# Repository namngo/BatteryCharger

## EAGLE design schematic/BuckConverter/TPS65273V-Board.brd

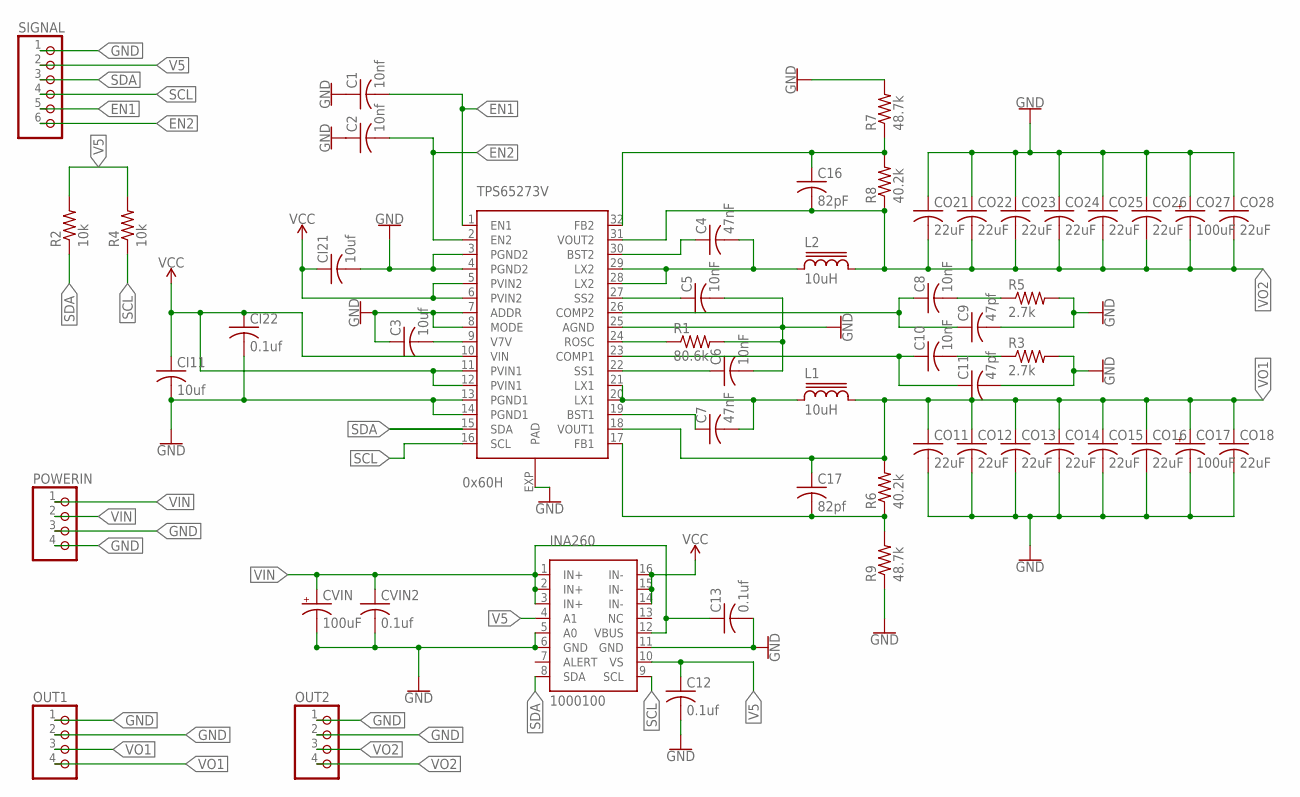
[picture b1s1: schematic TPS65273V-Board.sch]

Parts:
C1, C2: 10nf; C0805
C3: 10uf; C0805
C4, C7: 47nF; C0805
C5, C6, C8, C10: 10nF; C0805
C9, C11: 47pf; C0805
C12, C13: 0.1uf; C0805
C16: 82pF; C0805
C17: 82pf; C0805
CI11, CI21: 10uf; C1210
CI22: 0.1uf; C0805
CO11, CO12, CO13, CO14, CO15, CO16, CO18, CO21, CO22, CO23, CO24, CO25, CO26, CO28: 22uF; C0805
CO17, CO27: 100uF; PANASONIC_D
CVIN: 100uF; PANASONIC_D
CVIN2: 0.1uf; C0805
INA260: 1000100; TSSOP16
L1, L2: 10uH; MSS1048
OUT1, OUT2: PINHD-1X4; 1X04
POWERIN: PINHD-1X4; 1X04
R1: 80.6k; R0805
R2, R4: 10k; R0805
R3, R5: 2.7k; R0805
R6, R8: 40.2k; R0805
R7, R9: 48.7k; R0805
SIGNAL: PINHD-1X6; 1X06
TPS65273V: 0x60H; HTSSOP32DAP

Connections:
EN1: C1.2, SIGNAL.5, TPS65273V.1 (EN1)
EN2: C2.2, SIGNAL.6, TPS65273V.2 (EN2)
FB1: C17.2, R6.1, R9.2, TPS65273V.17 (FB1)
FB2: C16.1, R7.1, R8.2, TPS65273V.32 (FB2)
GND: C1.1, C2.1, C3.1, C5.2, C6.2, C9.2, C11.2, C12.2, C13.2, CI11.2, CI21.2, CI22.2, CO11.2, CO12.2, CO13.2, CO14.2, CO15.2, CO16.2, CO17.-, CO18.2, CO21.1, CO22.1, CO23.1, CO24.1, CO25.1, CO26.1, CO27.+, CO28.1, CVIN.-, CVIN2.2, INA260.5 (A0), INA260.6 (GND), INA260.11 (GND), OUT1.1, OUT1.2, OUT2.1, OUT2.2, POWERIN.3, POWERIN.4, R1.2, R3.2, R5.2, R7.2, R9.1, SIGNAL.1, TPS65273V.3 (PGND2), TPS65273V.4 (PGND2), TPS65273V.7 (ADDR), TPS65273V.8 (MODE), TPS65273V.13 (PGND1), TPS65273V.14 (PGND1), TPS65273V.25 (AGND), TPS65273V.EXP (PAD)
unnamed: C3.2, TPS65273V.9 (V7V)
unnamed: C4.2, L2.1, TPS65273V.28 (LX2), TPS65273V.29 (LX2)
unnamed: C4.1, TPS65273V.30 (BST2)
unnamed: C10.1, C11.1, TPS65273V.23 (COMP1)
unnamed: R1.1, TPS65273V.24 (ROSC)
unnamed: C10.2, R3.1
unnamed: C5.1, TPS65273V.27 (SS2)
unnamed: C8.1, C9.1, TPS65273V.26 (COMP2)
unnamed: C8.2, R5.1
unnamed: C6.1, TPS65273V.22 (SS1)
unnamed: C7.2, L1.1, TPS65273V.20 (LX1), TPS65273V.21 (LX1)
unnamed: C7.1, TPS65273V.19 (BST1)
SCL: INA260.9 (SCL), R4.1, SIGNAL.4, TPS65273V.16 (SCL)
SDA: INA260.8 (SDA), R2.1, SIGNAL.3, TPS65273V.15 (SDA)
V5: C12.1, INA260.4 (A1), INA260.10 (VS), R2.2, R4.2, SIGNAL.2
VCC: CI11.1, CI21.1, CI22.1, INA260.14 (IN-), INA260.15 (IN-), INA260.16 (IN-), TPS65273V.5 (PVIN2), TPS65273V.6 (PVIN2), TPS65273V.10 (VIN), TPS65273V.11 (PVIN1), TPS65273V.12 (PVIN1)
VIN: C13.1, CVIN.+, CVIN2.1, INA260.1 (IN+), INA260.2 (IN+), INA260.3 (IN+), INA260.12 (VBUS), POWERIN.1, POWERIN.2
VO1: C17.1, CO11.1, CO12.1, CO13.1, CO14.1, CO15.1, CO16.1, CO17.+, CO18.1, L1.2, OUT1.3, OUT1.4, R6.2, TPS65273V.18 (VOUT1)
VO2: C16.2, CO21.2, CO22.2, CO23.2, CO24.2, CO25.2, CO26.2, CO27.-, CO28.2, L2.2, OUT2.3, OUT2.4, R8.1, TPS65273V.31 (VOUT2)

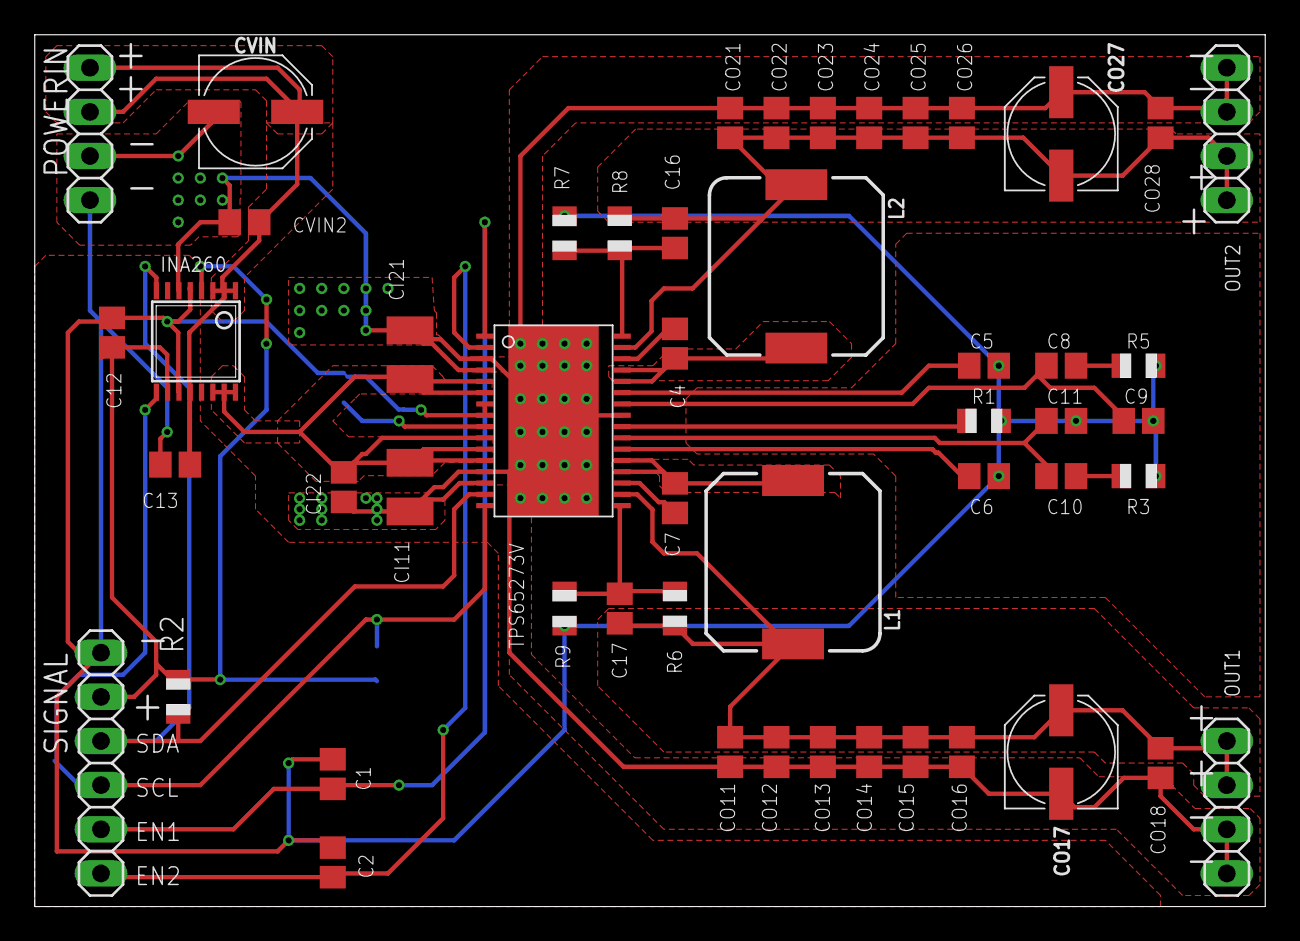
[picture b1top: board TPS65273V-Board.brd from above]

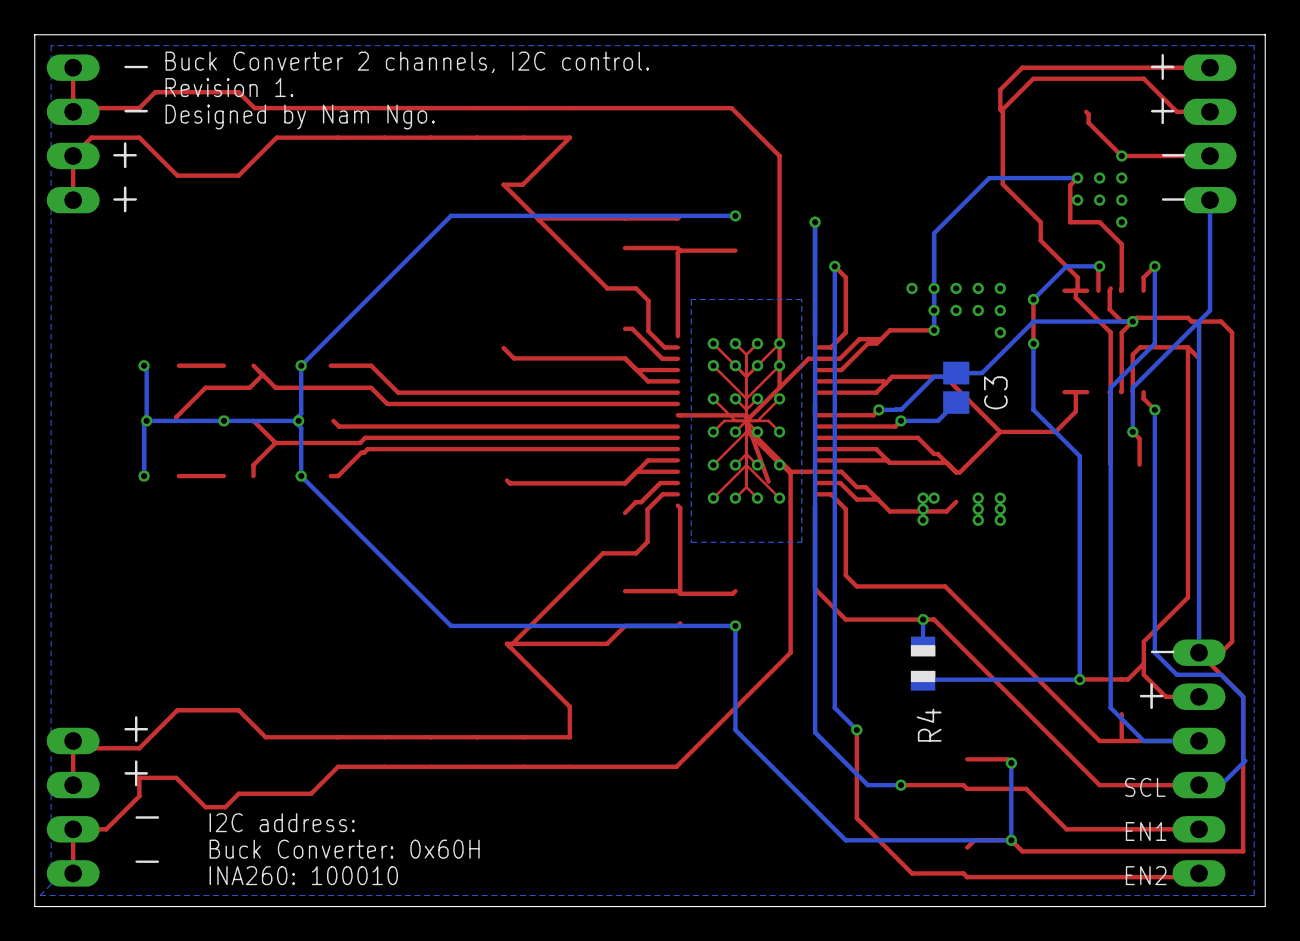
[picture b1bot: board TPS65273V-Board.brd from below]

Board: 2 copper layers, 70.8 x 50.2 mm, 53 parts (2 on the bottom side), 24 nets.

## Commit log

2017-09-09 first
2017-09-12 boards
2017-09-12 remove temp files
2017-09-13 files
2017-09-13 add gitignore
2017-09-13 design
2017-09-15 mostly done one half
2017-09-16 foo bar
2017-09-16 poly
2017-09-18 bottom ground pour
2017-09-19 done
2017-09-25 add main board

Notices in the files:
parts and their libraries:
SparkFun-Capacitors: Licensing: Creative Commons ShareAlike 4.0 International - https://creativecommons.org/licenses/by-sa/4.0
